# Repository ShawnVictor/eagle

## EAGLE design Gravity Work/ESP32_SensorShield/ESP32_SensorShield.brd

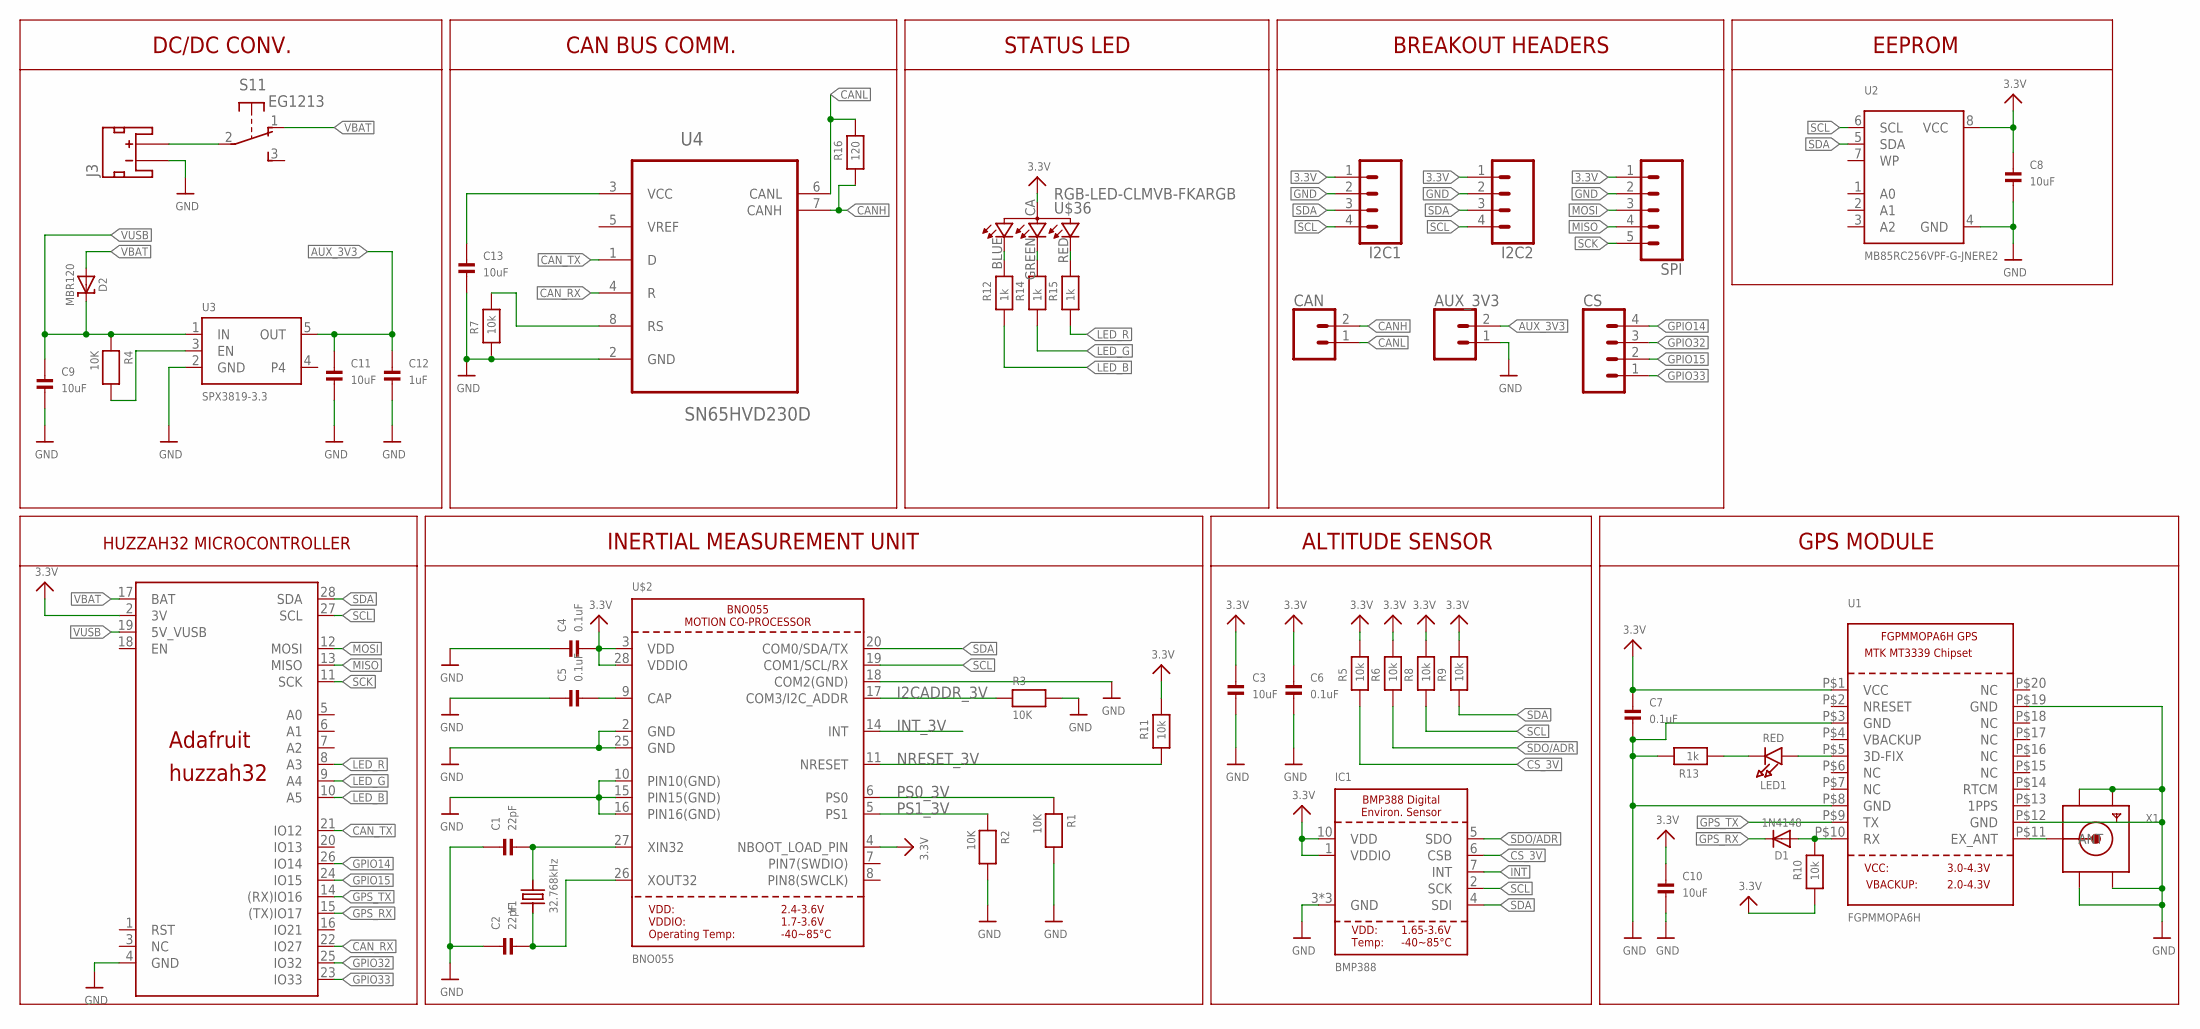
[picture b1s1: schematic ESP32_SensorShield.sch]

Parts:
AUX_3V3: CONN_02; 1X02
C1, C2: 22pF; 0603
C3, C8, C9, C10, C11, C13: 10uF; 0805
C4, C5, C6, C7: 0.1uF; 0603
C12: 1uF; 0805
CAN: CONN_02; 1X02
CS: CONN_04; 1X04
D1: 1N4148; SOD-323
D2: MBR120; SOD-123
I2C1, I2C2: CONN_04; 1X04
IC1: BMP388
J3: JST_2MM_MALE; JST-2-SMD
LED1: RED; CHIPLED_0805
R1, R2, R3, R4: 10K; 0603
R5, R6, R7, R8, R9, R10, R11: 10k; 0603
R12, R13, R14, R15: 1k; 0603
R16: 120; 0603
S1: EG1213
SPI: CONN_05; 1X05
U1: FGPMMOPA6H
U2: MB85RC256VPF-G-JNERE2; SOIC8_208MIL
U3: SPX3819-3.3; SOT23-5
U4: SN65HVD230D; SOIC127P600X175-8N
U$1: ADAFRUIT-FEATHER-HUZZAH32-SHIELD
U$2: BNO055
U$36: RGB-LED-CLMVB-FKARGB; PLCC4-2MM-RGB
X1: SMACONNECTOR_EDGE; SMA_EDGELAUNCH
Y1: 32.768kHz; CRYSTAL_8X3.8

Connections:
3.3V: C3.1, C4.2, C6.1, C7.1, C8.1, C10.1, I2C1.1, I2C2.1, IC1.1 (VDDIO), IC1.10 (VDD), R5.2, R6.2, R8.2, R9.2, R10.1, R11.2, SPI.1, U1.P$1 (VCC), U2.8 (VCC), U$1.2 (3V), U$2.3 (VDD), U$2.4 (NBOOT_LOAD_PIN), U$2.28 (VDDIO), U$36.CA (1)
AUX_3V3: AUX_3V3.2, C11.1, C12.1, U3.5 (OUT)
CANH: CAN.2, R16.1, U4.7 (CANH)
CANL: CAN.1, R16.2, U4.6 (CANL)
CAN_RX: U4.4 (R), U$1.22 (IO27)
CAN_TX: U4.1 (D), U$1.21 (IO12)
CS_3V: IC1.6 (CSB), R5.1
GND: AUX_3V3.1, C1.1, C2.1, C3.2, C4.1, C5.1, C6.2, C7.2, C8.2, C9.2, C10.2, C11.2, C12.2, C13.2, I2C1.2, I2C2.2, IC1.3 (GND), IC1.8 (GND), IC1.9 (GND), J3.1 (-), R1.2, R2.2, R3.2, R7.1, R13.2, SPI.2, U1.P$3 (GND), U1.P$8 (GND), U1.P$12 (GND), U1.P$19 (GND), U2.4 (GND), U3.2 (GND), U4.2 (GND), U$1.4 (GND), U$2.2 (GND), U$2.10 (PIN10(GND)), U$2.15 (PIN15(GND)), U$2.16 (PIN16(GND)), U$2.18 (COM2(GND)), U$2.25 (GND), X1.GND@1 (GND4), X1.GND@2 (GND3), X1.GND@3 (GND2), X1.GND@4 (GND1)
GPIO14: CS.4, U$1.26 (IO14)
GPIO15: CS.2, U$1.24 (IO15)
GPIO32: CS.3, U$1.25 (IO32)
GPIO33: CS.1, U$1.23 (IO33)
GPS_RX: D1.C, U$1.15 ((TX)IO17)
GPS_TX: U1.P$9 (TX), U$1.14 ((RX)IO16)
I2CADDR_3V: R3.1, U$2.17 (COM3/I2C_ADDR)
INT: IC1.7 (INT)
INT_3V: U$2.14 (INT)
LED_B: R12.1, U$1.10 (A5)
LED_G: R14.1, U$1.9 (A4)
LED_R: R15.1, U$1.8 (A3)
MISO: SPI.4, U$1.13 (MISO)
MOSI: SPI.3, U$1.12 (MOSI)
unnamed: C1.2, U$2.27 (XIN32), Y1.P$4 (2)
unnamed: C2.2, U$2.26 (XOUT32), Y1.P$1 (1)
unnamed: U1.P$11 (EX_ANT), X1.P (ANT)
unnamed: C5.2, U$2.9 (CAP)
unnamed: D1.A, R10.2, U1.P$10 (RX)
unnamed: J3.2 (+), S1.2
unnamed: C13.1, U4.3 (VCC)
unnamed: LED1.C, R13.1
unnamed: LED1.A, U1.P$5 (3D-FIX)
unnamed: R7.2, U4.8 (RS)
unnamed: R4.2, U3.3 (EN)
unnamed: R12.2, U$36.BLUE (2)
unnamed: R14.2, U$36.GREEN (3)
unnamed: R15.2, U$36.RED (4)
NRESET_3V: R11.1, U$2.11 (NRESET)
PS0_3V: R1.1, U$2.6 (PS0)
PS1_3V: R2.1, U$2.5 (PS1)
SCK: SPI.5, U$1.11 (SCK)
SCL: I2C1.4, I2C2.4, IC1.2 (SCK), R8.1, U2.6 (SCL), U$1.27 (SCL), U$2.19 (COM1/SCL/RX)
SDA: I2C1.3, I2C2.3, IC1.4 (SDI), R9.1, U2.5 (SDA), U$1.28 (SDA), U$2.20 (COM0/SDA/TX)
SDO/ADR: IC1.5 (SDO), R6.1
VBAT: D2.A, S1.1 (O), U$1.17 (BAT)
VUSB: C9.1, D2.C, R4.1, U3.1 (IN), U$1.19 (5V_VUSB)

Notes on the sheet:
HUZZAH32 MICROCONTROLLER
INERTIAL MEASUREMENT UNIT
ALTITUDE SENSOR
GPS MODULE
EEPROM
DC/DC CONV.
CAN BUS COMM.
STATUS LED
BREAKOUT HEADERS

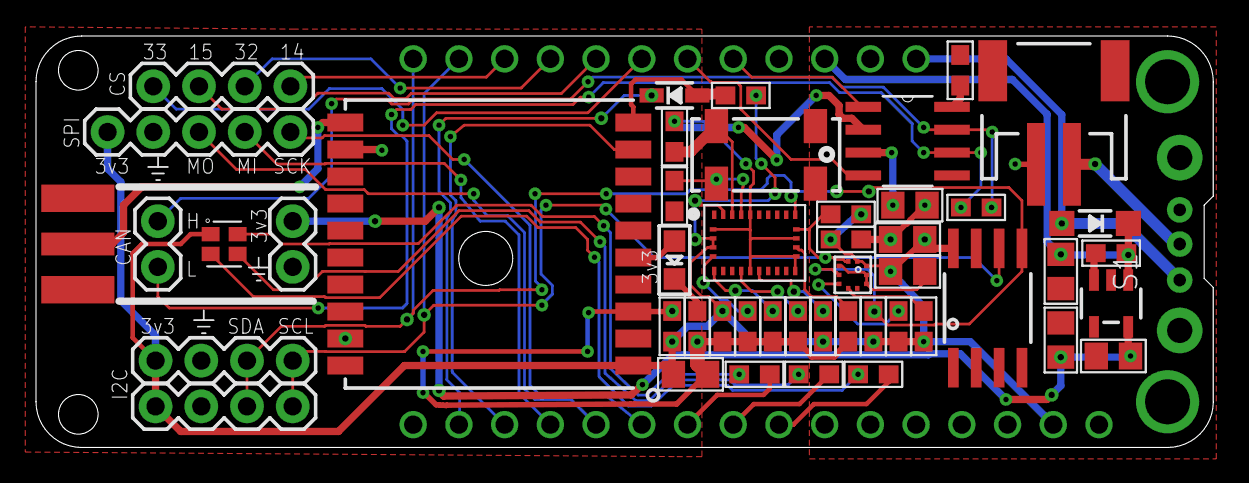
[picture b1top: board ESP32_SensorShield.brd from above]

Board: 2 copper layers, 65.4 x 22.9 mm, 50 parts (1 on the bottom side), 43 nets.

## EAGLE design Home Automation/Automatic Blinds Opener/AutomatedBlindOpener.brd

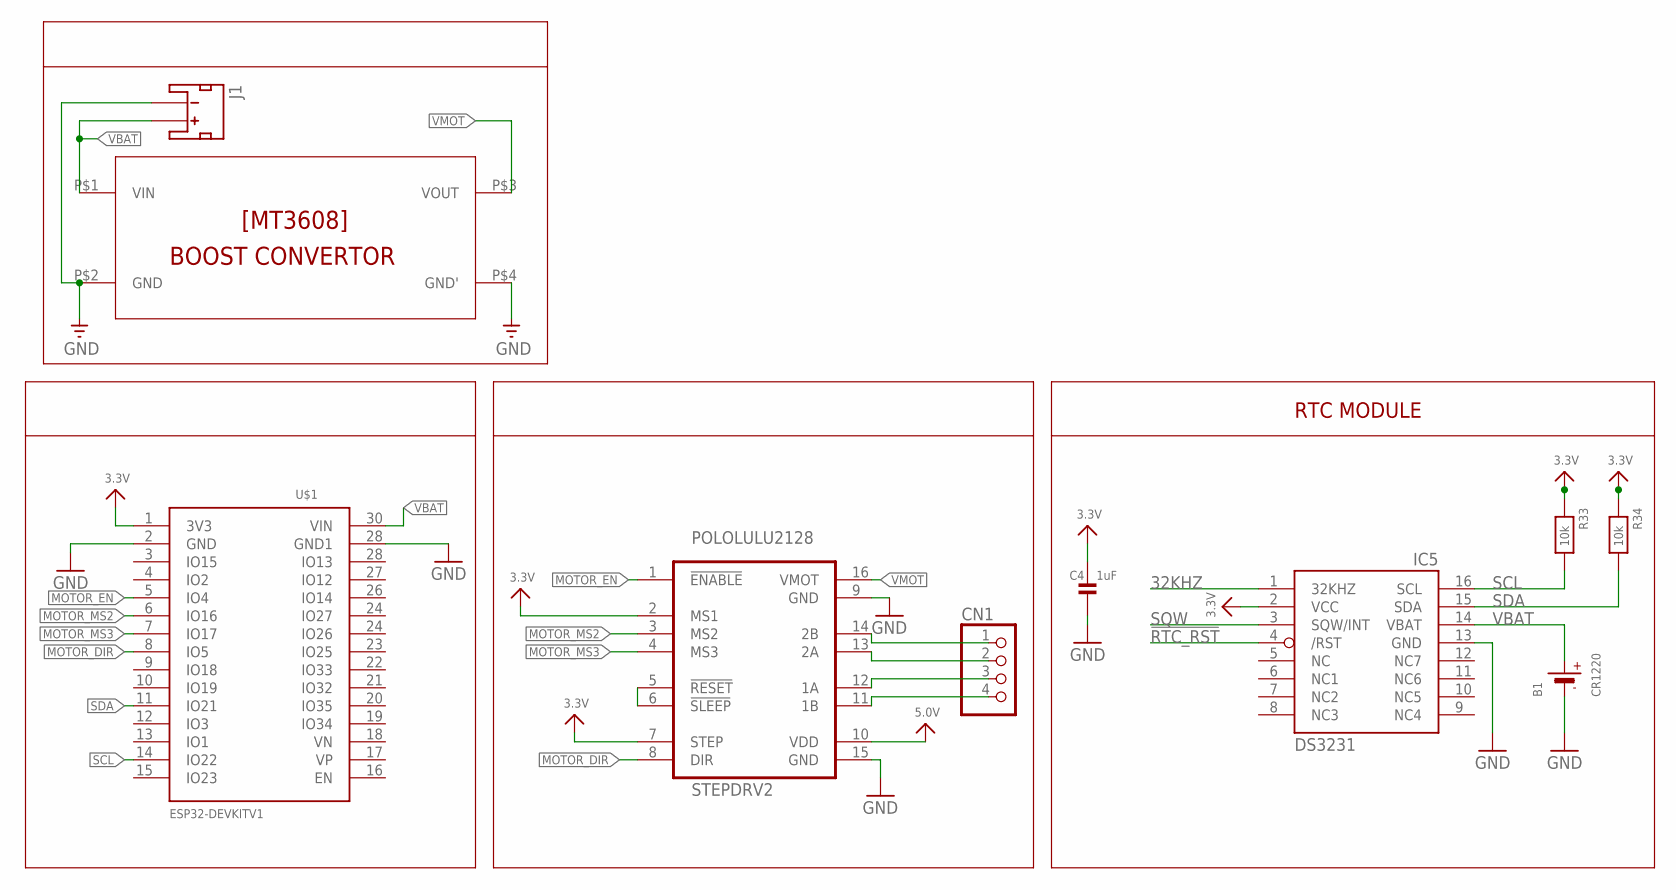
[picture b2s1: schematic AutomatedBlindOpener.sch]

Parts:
B1: CR1220
C4: 1uF; 0805
CN1: JST_4PIN; JSTPH4
IC5: DS3231/SO; SO16W
J1: JST_2MM_MALE; JST-2-SMD
R33, R34: 10k; 0805
STEPDRV2: POLOLULU2128
U$1: ESP32DEVKITV1; ESP32-DEVKITV1
U$3: MT3608

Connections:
3.3V: C4.2, IC5.2 (VCC), R33.1, R34.1, STEPDRV2.2 (MS1), STEPDRV2.7 (STEP), U$1.1 (3V3)
5.0V: STEPDRV2.10 (VDD)
32KHZ: IC5.1 (32KHZ)
!RTC_RST: IC5.4 (/RST)
GND: B1.-, C4.1, IC5.13 (GND), J1.1 (-), STEPDRV2.9 (GND), STEPDRV2.15 (GND), U$1.2 (GND), U$1.28 (IO13), U$3.P$2 (GND), U$3.P$4 (GND')
MOTOR_DIR: STEPDRV2.8 (DIR), U$1.8 (IO5)
MOTOR_EN: STEPDRV2.1 (!ENABLE), U$1.5 (IO4)
MOTOR_MS2: STEPDRV2.3 (MS2), U$1.6 (IO16)
MOTOR_MS3: STEPDRV2.4 (MS3), U$1.7 (IO17)
unnamed: CN1.1, STEPDRV2.14 (2B)
unnamed: CN1.2, STEPDRV2.13 (2A)
unnamed: CN1.3, STEPDRV2.12 (1A)
unnamed: CN1.4, STEPDRV2.11 (1B)
unnamed: STEPDRV2.5 (!RESET), STEPDRV2.6 (!SLEEP)
SCL: IC5.16 (SCL), R33.2, U$1.14 (IO22)
SDA: IC5.15 (SDA), R34.2, U$1.11 (IO21)
SQW: IC5.3 (SQW/INT)
VBAT: B1.+$1 (+), IC5.14 (VBAT), J1.2 (+), U$1.30 (VIN), U$3.P$1 (VIN)
VMOT: STEPDRV2.16 (VMOT), U$3.P$3 (VOUT)

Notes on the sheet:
RTC MODULE

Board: 2 copper layers, 10 parts (1 on the bottom side), 15 nets, no tracks yet.

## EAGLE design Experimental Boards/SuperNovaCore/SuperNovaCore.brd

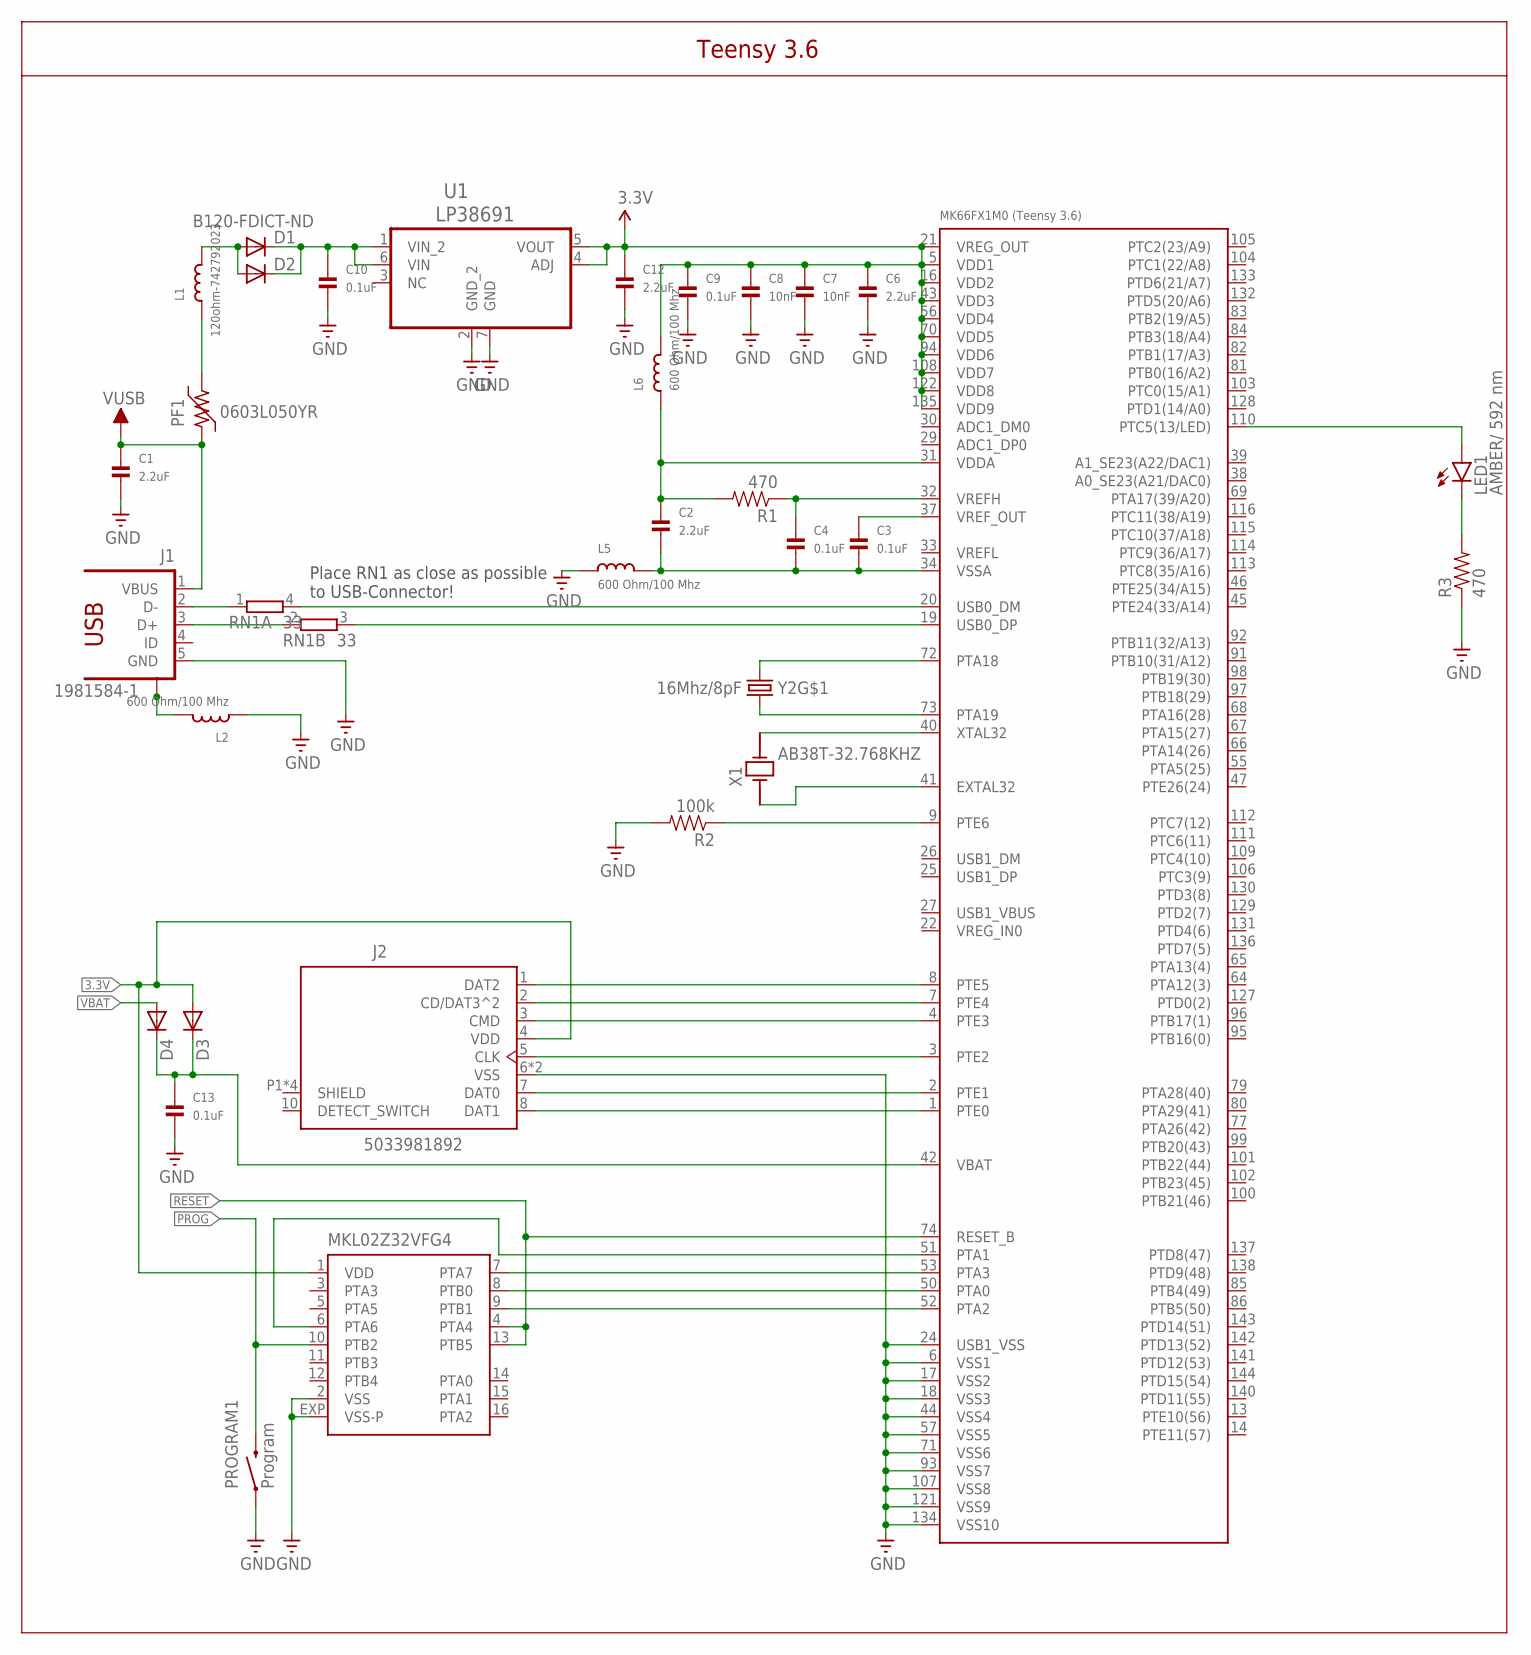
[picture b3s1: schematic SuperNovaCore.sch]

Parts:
C1, C2, C6, C12: 2.2uF; 0603
C3, C4, C9, C10, C13: 0.1uF; 0603
C7, C8: 10nF; 0603
D1, D2, D3, D4: B120-FDICT-ND; DO214AC
J1: 1981584-1; MPN ZX62-AB-5PA(11)
J2: 503398-1892; MOLEX_503398-1892
L1: 120ohm-742792023; 0805
L2, L5, L6: 600 Ohm/100 Mhz; 0805
LED1: AMBER/ 592 nm; LED-0603
PF1: 0603L050YR; F0603
PROGRAM1: Program; TACTILE-SWITCH-1101NE; MPN RS-282G05A3-SM RT
R1, R3: 470; 0603-RES
R2: 100k; 0603-RES
RN1: 33; EXB34V; MPN EXB-34V330JV
U1: LP38691SD-ADJ; DFN300X300X80-7N
U$1: MK66FX1M0; LQFP144
U$2: MKL02Z32VFG4; QFN16
X1: AB38T-32.768KHZ; XTAL_AB38T-32.768KHZ
Y2: 16Mhz/8pF; CRYSTAL-SMD-5X3; MPN ECS-160-8-30B-CKM

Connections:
3.3V: C6.1, C7.1, C8.1, C9.1, C12.1, D3.A, J2.4 (VDD), L6.2, U1.4 (ADJ), U1.5 (VOUT), U$1.5 (VDD1), U$1.16 (VDD2), U$1.21 (VREG_OUT), U$1.43 (VDD3), U$1.56 (VDD4), U$1.70 (VDD5), U$1.94 (VDD6), U$1.108 (VDD7), U$1.122 (VDD8), U$1.135 (VDD9), U$2.1 (VDD)
GND: C1.2, C6.2, C7.2, C8.2, C9.2, C10.2, C12.2, C13.2, J1.5 (GND), J2.6 (VSS), J2.9 (VSS), L2.1, L5.1, PROGRAM1.P$1 (1), R2.2, R3.1, U1.2 (GND_2), U1.7 (GND), U$1.6 (VSS1), U$1.17 (VSS2), U$1.18 (VSS3), U$1.24 (USB1_VSS), U$1.44 (VSS4), U$1.57 (VSS5), U$1.71 (VSS6), U$1.93 (VSS7), U$1.107 (VSS8), U$1.121 (VSS9), U$1.134 (VSS10), U$2.2 (VSS), U$2.EXP (VSS-P)
unnamed: RN1.3 (2), U$1.19 (USB0_DP)
unnamed: C10.1, D1.C, D2.C, U1.1 (VIN_2), U1.6 (VIN)
unnamed: L1.1, PF1.2
unnamed: D1.A, D2.A, L1.2
unnamed: J2.1 (DAT2), U$1.8 (PTE5)
unnamed: J2.2 (CD/DAT3^2), U$1.7 (PTE4)
unnamed: RN1.4 (2), U$1.20 (USB0_DM)
unnamed: C2.2, C3.2, C4.2, L5.2, U$1.34 (VSSA)
unnamed: C2.1, L6.1, R1.2, U$1.31 (VDDA)
unnamed: C4.1, R1.1, U$1.32 (VREFH)
unnamed: C3.1, U$1.37 (VREF_OUT)
unnamed: J2.3 (CMD), U$1.4 (PTE3)
unnamed: J2.5 (CLK), U$1.3 (PTE2)
unnamed: J2.7 (DAT0), U$1.2 (PTE1)
unnamed: J2.8 (DAT1), U$1.1 (PTE0)
unnamed: U$1.72 (PTA18), Y2.3 (2)
unnamed: C13.1, D3.C, D4.C, U$1.42 (VBAT)
unnamed: U$1.73 (PTA19), Y2.1
unnamed: U$1.40 (XTAL32), X1.2
unnamed: U$1.41 (EXTAL32), X1.1
unnamed: R2.1, U$1.9 (PTE6)
unnamed: U$1.51 (PTA1), U$2.6 (PTA6)
unnamed: U$1.53 (PTA3), U$2.7 (PTA7)
unnamed: U$1.50 (PTA0), U$2.8 (PTB0)
unnamed: U$1.52 (PTA2), U$2.9 (PTB1)
unnamed: LED1.A, U$1.110 (PTC5(13/LED))
unnamed: LED1.C, R3.2
PROG: PROGRAM1.P$2 (2), U$2.10 (PTB2)
RESET: U$1.74 (RESET_B), U$2.4 (PTA4), U$2.13 (PTB5)
USB_CON_N: J1.2 (D-), RN1.1
USB_CON_P: J1.3 (D+), RN1.2 (1)
USB_SHIELD: J1.S1, J1.S2, J1.S3, J1.S4, L2.2
VBAT: D4.A
VUSB: C1.1, J1.1 (VBUS), PF1.1

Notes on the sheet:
Teensy 3.6
Place RN1 as close as possible to USB-Connector!

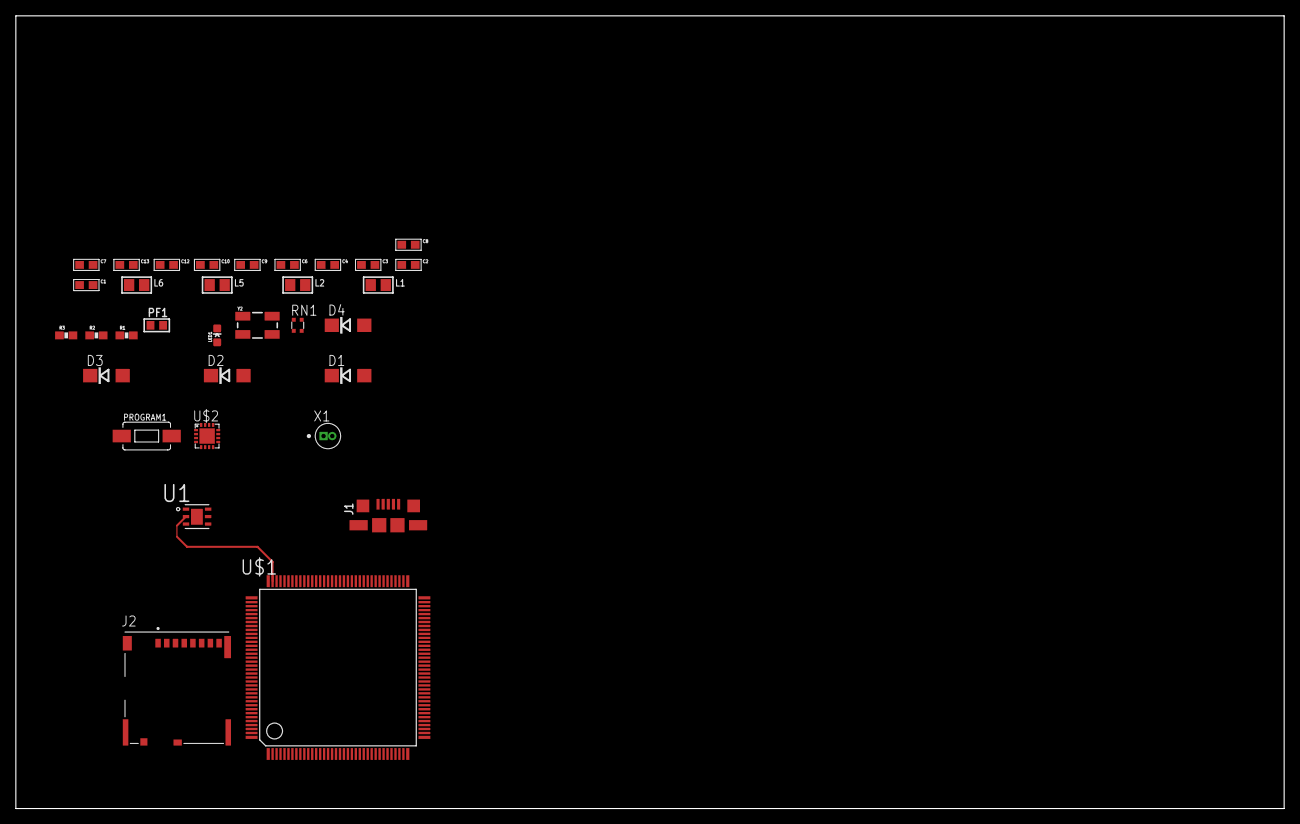
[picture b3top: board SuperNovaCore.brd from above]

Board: 2 copper layers, 160.0 x 100.0 mm, 33 parts (0 on the bottom side), 35 nets.

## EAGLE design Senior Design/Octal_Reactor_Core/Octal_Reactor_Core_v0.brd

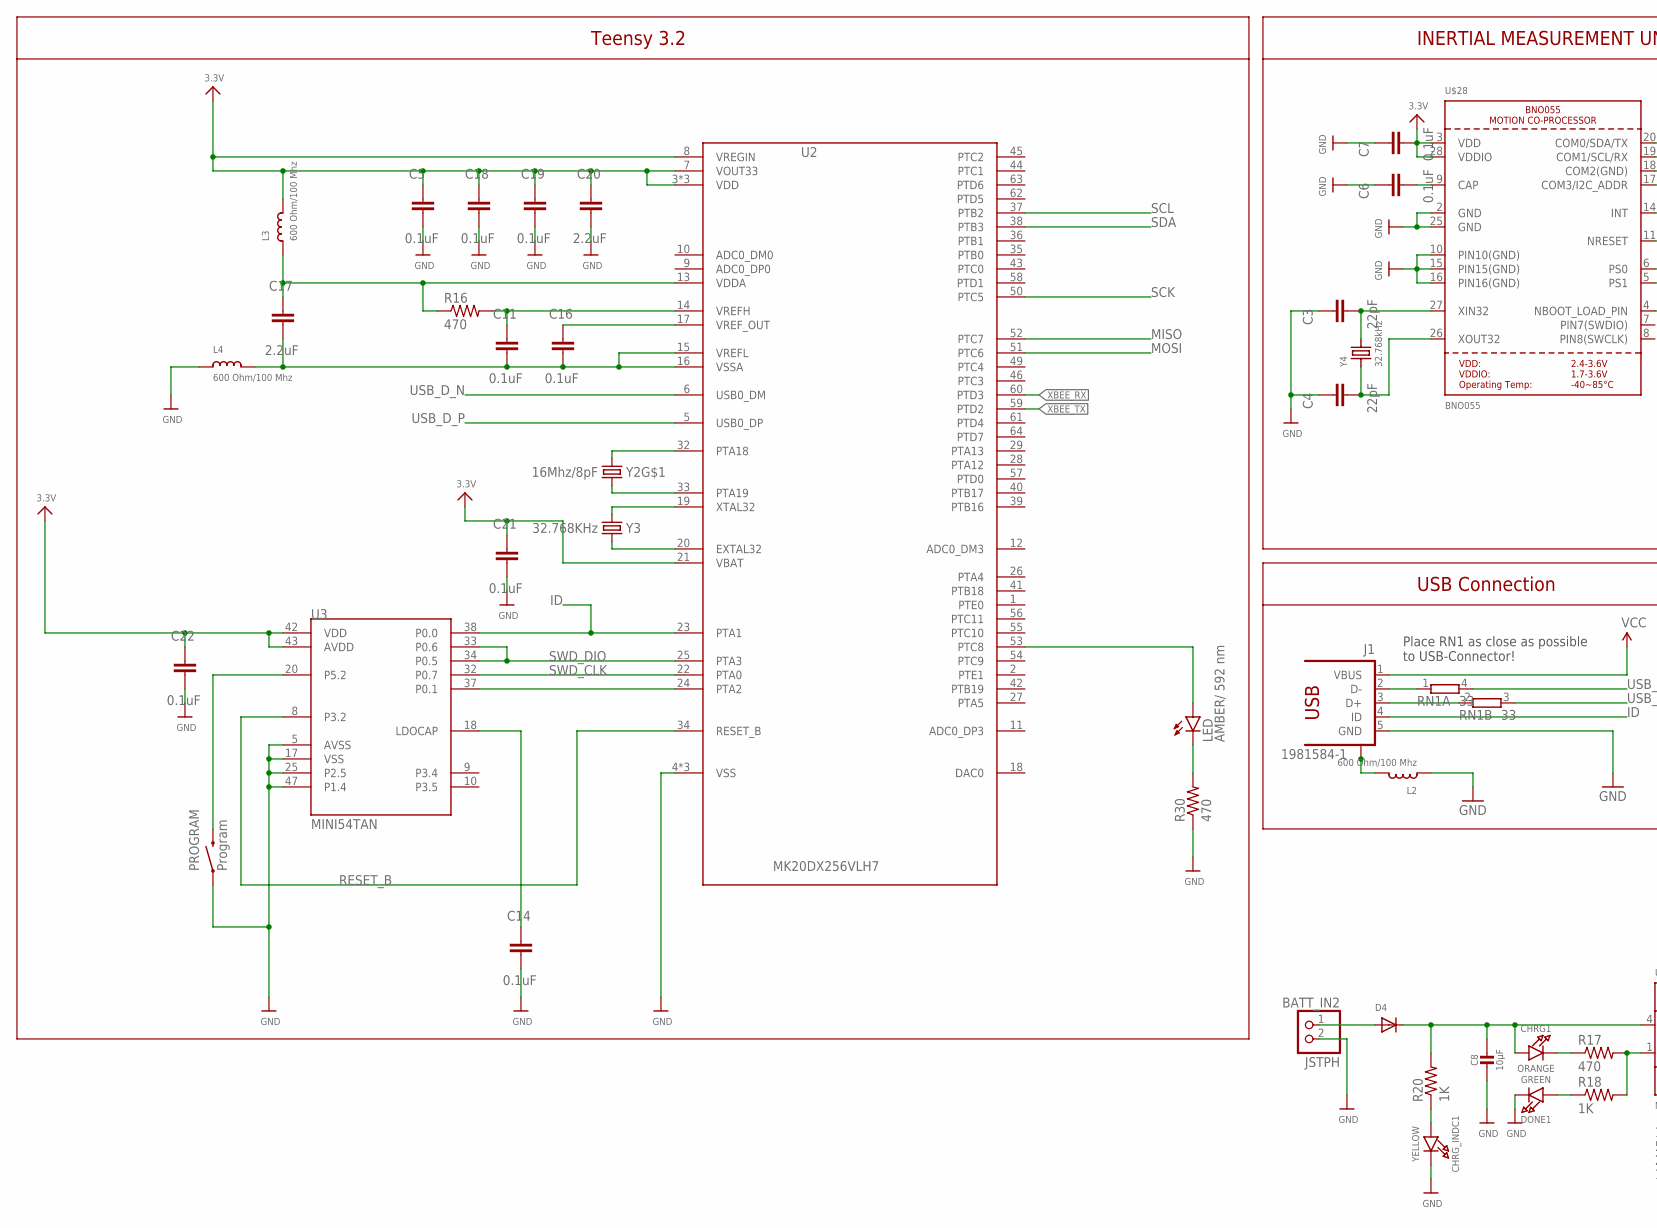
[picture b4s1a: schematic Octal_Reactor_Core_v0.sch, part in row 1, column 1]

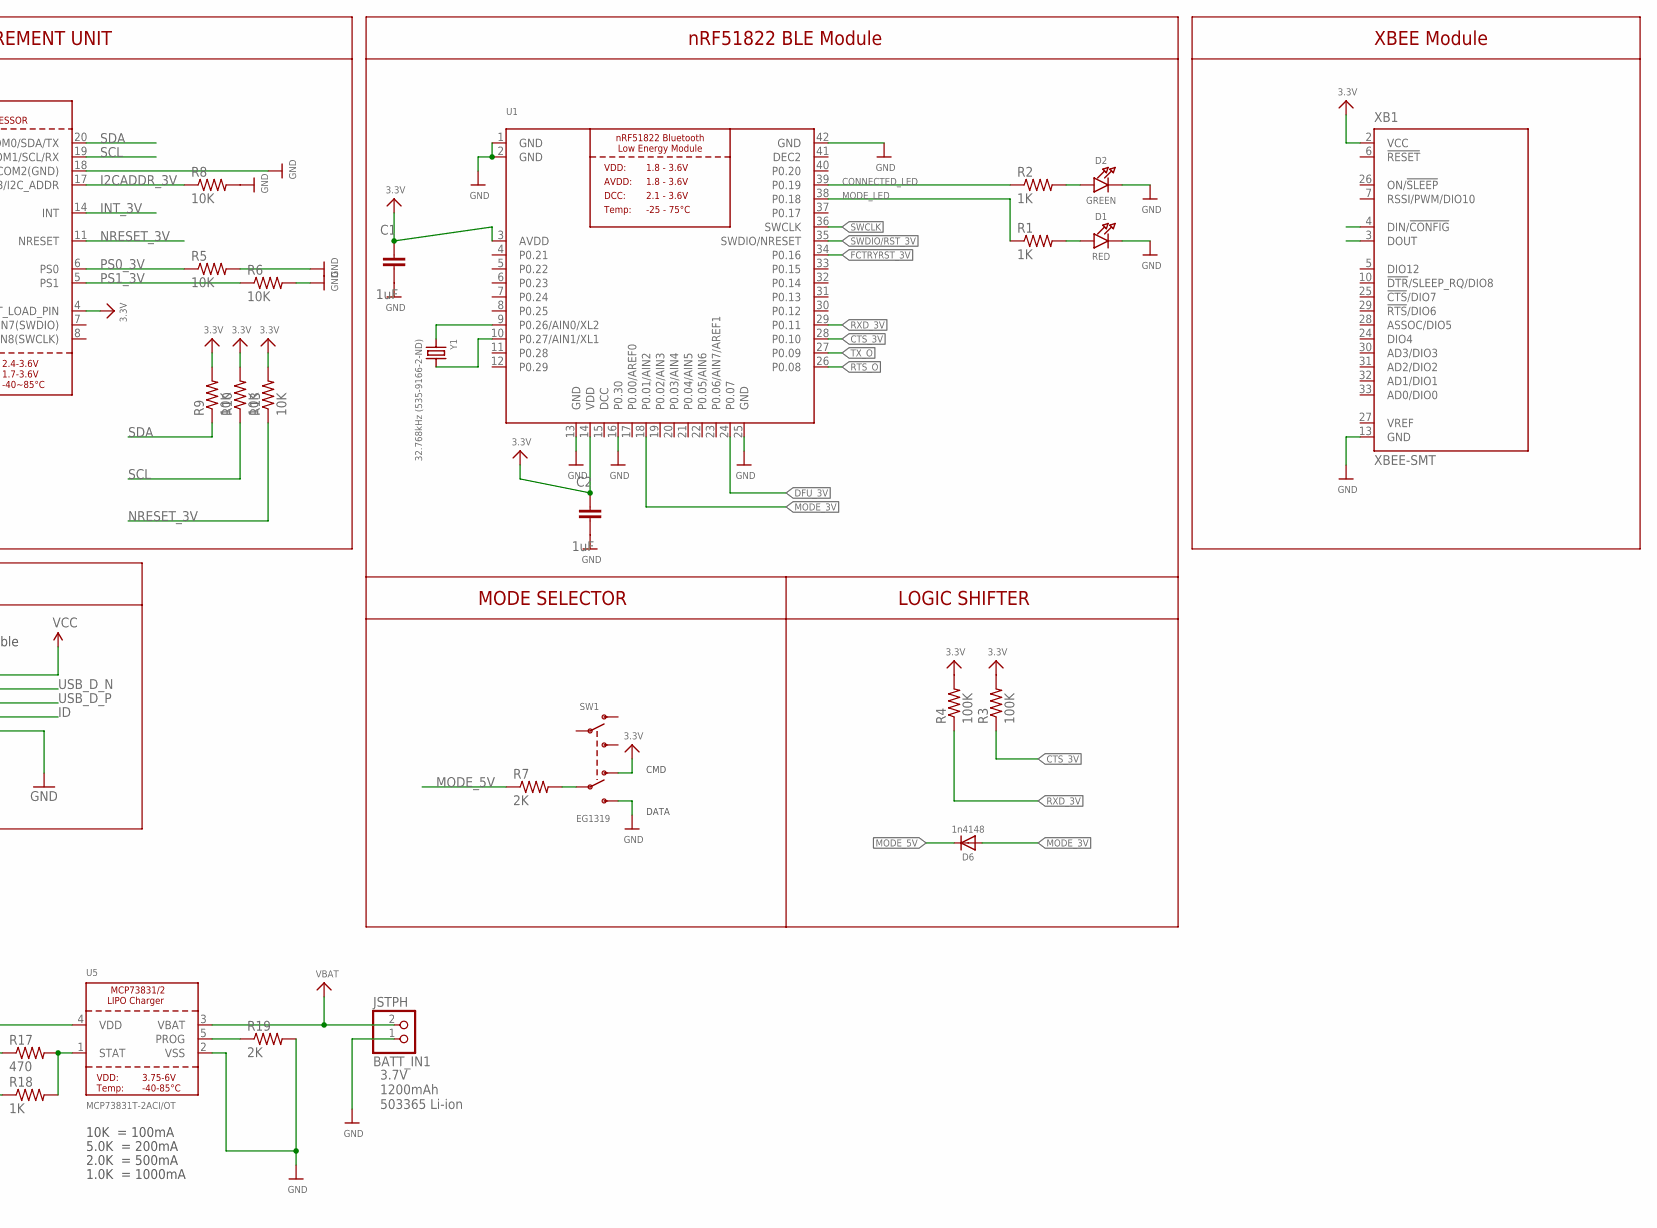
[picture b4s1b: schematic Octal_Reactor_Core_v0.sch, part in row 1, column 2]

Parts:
BATT_IN1, BATT_IN2: JSTPH; JSTPH2
C1, C2: 1uF; CAP_0402
C3, C4: 22pF; CAP_0402
C5, C6, C7, C11, C14, C16, C18, C19, C21, C22: 0.1uF; CAP_0402
C8: 10µF; 0805-NO
C17, C20: 2.2uF; CAP_0402
CHRG1: ORANGE; CHIPLED_0805_NOOUTLINE
CHRG_INDC1: YELLOW; CHIPLED_0805_NOOUTLINE
D1: RED; CHIPLED_0805_NOOUTLINE
D2: GREEN; CHIPLED_0805_NOOUTLINE
D4: DIODESOD-123; SOD-123
D6: 1n4148; SOD-323
DONE1: GREEN; CHIPLED_0805_NOOUTLINE
J1: 1981584-1; MPN ZX62-AB-5PA(11)
L2, L3, L4: 600 Ohm/100 Mhz; 0805
LED: AMBER/ 592 nm; LED-0603
PROGRAM: Program; TACTILE-SWITCH-1101NE; MPN RS-282G05A3-SM RT
R1, R2, R18, R20: 1K; RES_0402
R3, R4: 100K; RES_0402
R5, R6, R8, R9, R10, R13: 10K; RES_0402
R7, R19: 2K; RES_0402
R16, R17: 470; RES_0402
R30: 470; 0603-RES
RN1: 33; EXB34V; MPN EXB-34V330JV
SW1: EG1319; EG1390
U1: NRF51822_MODULE_MDBT40; BLE_MODULE_RAYTAC_MDBT40
U2: MK20DX256VLH7; MPN MK20DX256VLH7
U3: MINI54TAN
U5: MCP73831T-2ACI/OT; SOT23-5
U$28: BNO055
XB1: XBEE-SMT
Y1: 32.768kHz (535-9166-2-ND); CRYSTAL_CYL_2X6MM_SMT
Y2: 16Mhz/8pF; CRYSTAL-SMD-5X3; MPN ECS-160-8-30B-CKM
Y3: 32.768KHz; CRYSTAL-TXC-7A; MPN FC-255 32.7680K-A3
Y4: 32.768kHz; CRYSTAL_8X3.8

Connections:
3.3V: C1.1, C2.1, C5.1, C7.2, C18.1, C19.1, C20.1, C21.1, C22.1, L3.2, R3.2, R4.2, R9.2, R10.2, R13.2, SW1.O2, U1.3 (AVDD), U1.14 (VDD), U2.3 (VDD), U2.7 (VOUT33), U2.8 (VREGIN), U2.21 (VBAT), U2.30 (VDD), U2.48 (VDD), U3.42 (VDD), U3.43 (AVDD), U$28.3 (VDD), U$28.4 (NBOOT_LOAD_PIN), U$28.28 (VDDIO), XB1.2 (VCC)
CONNECTED_LED: R2.1, U1.39 (P0.19)
CTS_3V: R3.1, U1.28 (P0.10)
DCC: U1.15 (DCC)
DEC2: U1.41 (DEC2)
DFU_3V: U1.24 (P0.07)
FCTRYRST_3V: U1.34 (P0.16)
GND: BATT_IN1.1, BATT_IN2.2, C1.2, C2.2, C3.1, C4.1, C5.2, C6.1, C7.1, C8.2, C14.2, C18.2, C19.2, C20.2, C21.2, C22.2, CHRG_INDC1.C, D1.C, D2.C, DONE1.C, J1.5 (GND), L2.1, L4.1, PROGRAM.P$1 (1), R5.2, R6.2, R8.2, R19.2, R30.1, SW1.S2, U1.1 (GND), U1.2 (GND), U1.13 (GND), U1.16 (P0.30), U1.25 (GND), U1.42 (GND), U2.4 (VSS), U2.31 (VSS), U2.47 (VSS), U3.5 (AVSS), U3.17 (VSS), U3.25 (P2.5), U3.47 (P1.4), U5.2 (VSS), U$28.2 (GND), U$28.10 (PIN10(GND)), U$28.15 (PIN15(GND)), U$28.16 (PIN16(GND)), U$28.18 (COM2(GND)), U$28.25 (GND), XB1.13 (GND)
I2CADDR_3V: R8.1, U$28.17 (COM3/I2C_ADDR)
ID: J1.4 (ID), U2.23 (PTA1), U3.38 (P0.0)
INT_3V: U$28.14 (INT)
MISO: U2.52 (PTC7)
MODE_3V: D6.A, U1.18 (P0.01/AIN2)
MODE_5V: D6.C, R7.1
MODE_LED: R1.1, U1.38 (P0.18)
MOSI: U2.51 (PTC6)
unnamed: U1.9 (P0.26/AIN0/XL2), Y1.1
unnamed: U1.10 (P0.27/AIN1/XL1), Y1.2
unnamed: C3.2, U$28.27 (XIN32), Y4.P$4 (2)
unnamed: R7.2, SW1.P2
unnamed: D1.A, R1.2
unnamed: D2.A, R2.2
unnamed: C4.2, U$28.26 (XOUT32), Y4.P$1 (1)
unnamed: C6.2, U$28.9 (CAP)
unnamed: LED.A, U2.53 (PTC8)
unnamed: U2.24 (PTA2), U3.37 (P0.1)
unnamed: CHRG1.C, R17.1
unnamed: LED.C, R30.2
unnamed: PROGRAM.P$2 (2), U3.20 (P5.2)
unnamed: C14.1, U3.18 (LDOCAP)
unnamed: R17.2, R18.2, U5.1 (STAT)
unnamed: R19.1, U5.5 (PROG)
unnamed: U2.32 (PTA18), Y2.3 (2)
unnamed: U2.33 (PTA19), Y2.1
unnamed: U2.19 (XTAL32), Y3.P$2 (2)
unnamed: U2.20 (EXTAL32), Y3.P$1 (1)
unnamed: DONE1.A, R18.1
unnamed: C8.1, CHRG1.A, D4.C, R20.2, U5.4 (VDD)
unnamed: CHRG_INDC1.A, R20.1
NRESET_3V: R13.1, U$28.11 (NRESET)
PS0_3V: R5.1, U$28.6 (PS0)
PS1_3V: R6.1, U$28.5 (PS1)
RESET_B: U2.34 (RESET_B), U3.8 (P3.2)
RTS_O: U1.26 (P0.08)
RXD_3V: R4.1, U1.29 (P0.11)
SCK: U2.50 (PTC5)
SCL: R10.1, U2.37 (PTB2), U$28.19 (COM1/SCL/RX)
SDA: R9.1, U2.38 (PTB3), U$28.20 (COM0/SDA/TX)
SWCLK: U1.36 (SWCLK)
SWDIO/RST_3V: U1.35 (SWDIO/NRESET)
SWD_CLK: U2.22 (PTA0), U3.32 (P0.7)
SWD_DIO: U2.25 (PTA3), U3.33 (P0.6), U3.34 (P0.5)
TX_O: U1.27 (P0.09)
USB_CON_N: J1.2 (D-), RN1.1
USB_CON_P: J1.3 (D+), RN1.2 (1)
USB_D_N: RN1.4 (2), U2.6 (USB0_DM)
USB_D_P: RN1.3 (2), U2.5 (USB0_DP)
USB_SHIELD: J1.S1, J1.S2, J1.S3, J1.S4, L2.2
VBAT: BATT_IN1.2, U5.3 (VBAT)
VCC: J1.1 (VBUS)
VDDA: C17.1, L3.1, R16.1, U2.13 (VDDA)
VREFH: C11.1, R16.2, U2.14 (VREFH)
VREFL: C11.2, C16.2, C17.2, L4.2, U2.15 (VREFL), U2.16 (VSSA)
VREF_OUT: C16.1, U2.17 (VREF_OUT)
VUSB: BATT_IN2.1, D4.A
XBEE_RX: U2.60 (PTD3)
XBEE_TX: U2.59 (PTD2)

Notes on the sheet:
nRF51822 BLE Module
XBEE Module
DATA
CMD
MODE SELECTOR
LOGIC SHIFTER
Teensy 3.2
Place RN1 as close as possible to USB-Connector!
USB Connection
10K = 100mA
5.0K = 200mA
2.0K = 500mA
1.0K = 1000mA
3.7V 1200mAh 503365 Li-ion
INERTIAL MEASUREMENT UNIT

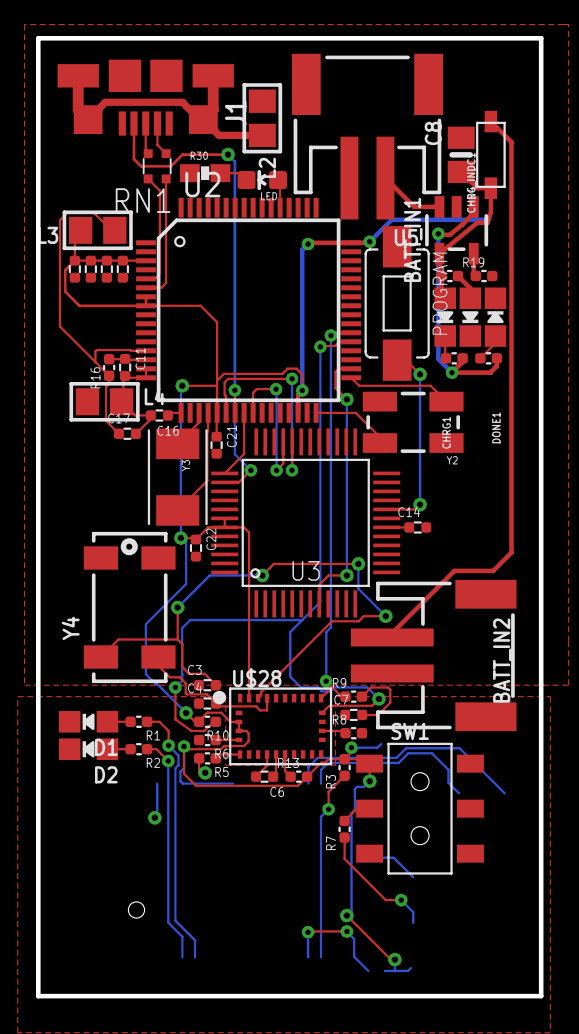
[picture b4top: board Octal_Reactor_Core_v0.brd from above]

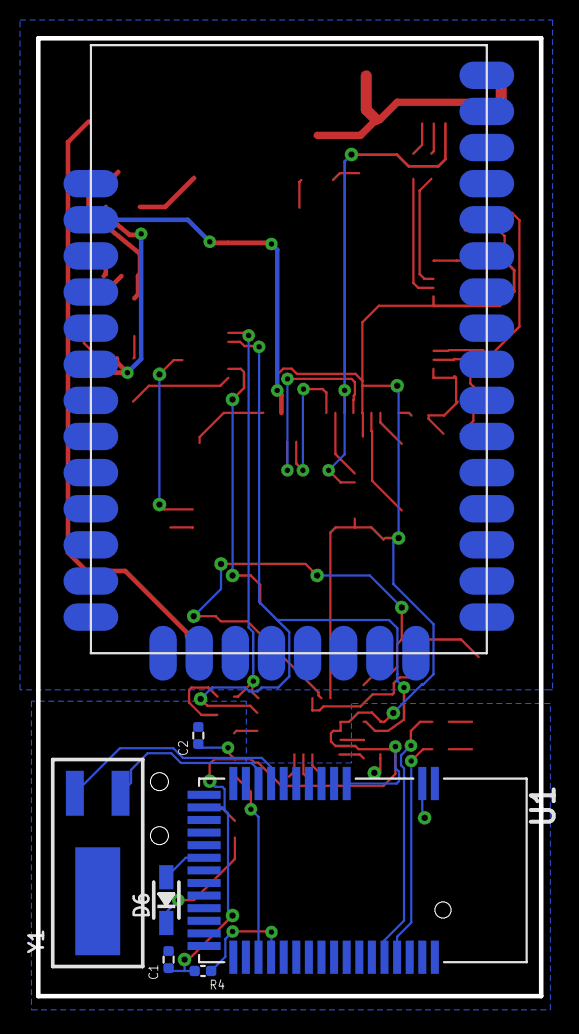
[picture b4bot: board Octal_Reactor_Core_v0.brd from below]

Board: 2 copper layers, 27.9 x 53.2 mm, 61 parts (7 on the bottom side), 52 nets.

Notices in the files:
parts and their libraries:
SparkFun-Electromechanical: Licensing: Creative Commons ShareAlike 4.0 International - https://creativecommons.org/licenses/by-sa/4.0
con-usb: Copyright (C) 2008, Bob Starr
supply0: Copyright (C) 2007, Bob Starr
dframes: Copyright (C) 2004, Bob Starr (bobstarr@mindspring.com)
